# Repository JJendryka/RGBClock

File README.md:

# RGBClock
ESP8266 based RGB clock system for schools with time and schedule synchronization

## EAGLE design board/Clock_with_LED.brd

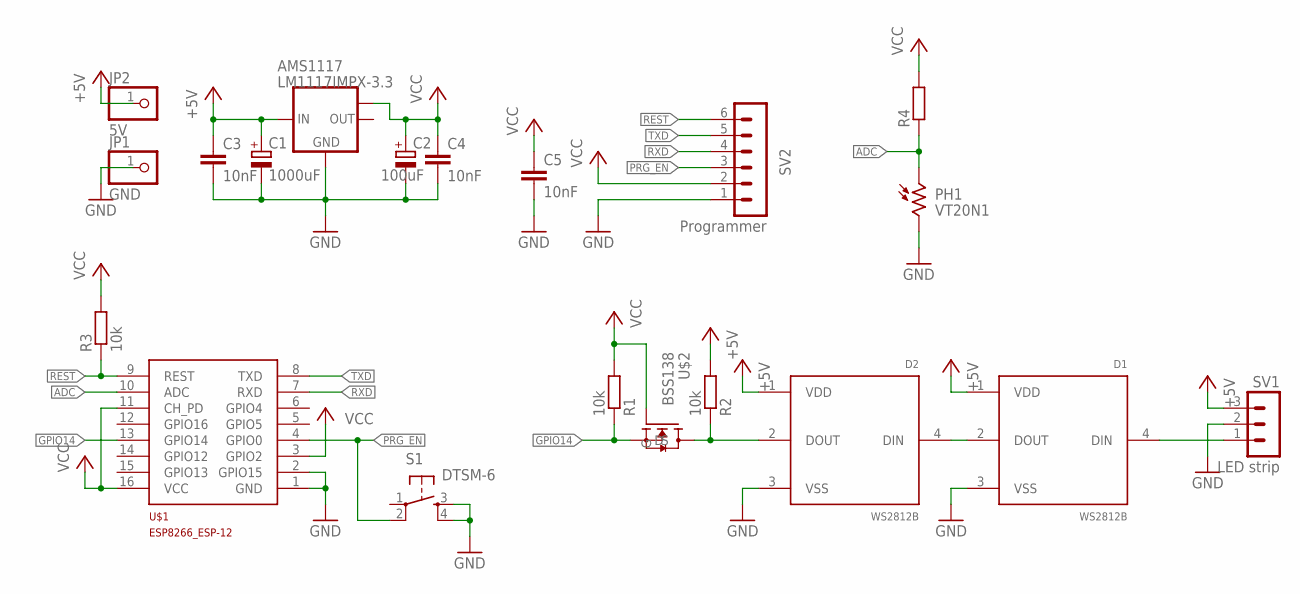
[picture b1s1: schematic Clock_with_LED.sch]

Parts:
AMS1117: LM1117IMPX-3.3; SOT223
C1: 1000uF; TT5D11L
C2: 100uF; TT5D7L
C3, C4, C5: 10nF; C0805
D1, D2: WS2812B; LED_WS2812B
JP1: GND; 1X01
JP2: 5V; 1X01
PH1: VT20N1; TO46-VT200
R1, R2, R3: 10k; R0805
R4: R-EU_R0805; R0805
S1: DTSM-6
SV1: LED strip; MA03-1
SV2: Programmer; MA06-1
U$1: ESP8266_ESP-12; ESP8266-ESP12
U$2: BSS138

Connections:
+5V: AMS1117.3 (IN), C1.+, C3.1, D1.1 (VDD), D2.1 (VDD), JP2.1, R2.2, SV1.3
ADC: PH1.1, R4.1, U$1.10 (ADC)
GND: AMS1117.1 (GND), C1.-, C2.-, C3.2, C4.2, C5.2, D1.3 (VSS), D2.3 (VSS), JP1.1, PH1.2, S1.3, S1.4, SV1.2, SV2.1, U$1.1 (GND), U$1.2 (GPIO15)
GPIO14: R1.1, U$1.13 (GPIO14), U$2.S
unnamed: D1.2 (DOUT), D2.4 (DIN)
unnamed: D1.4 (DIN), SV1.1
unnamed: D2.2 (DOUT), R2.1, U$2.D
PRG_EN: S1.2, SV2.3, U$1.4 (GPIO0)
REST: R3.1, SV2.6, U$1.9 (REST)
RXD: SV2.4, U$1.7 (RXD)
TXD: SV2.5, U$1.8 (TXD)
VCC: AMS1117.TAB (OUT1), C2.+, C4.1, C5.1, R1.2, R3.2, R4.2, SV2.2, U$1.3 (GPIO2), U$1.11 (CH_PD), U$1.16 (VCC), U$2.G

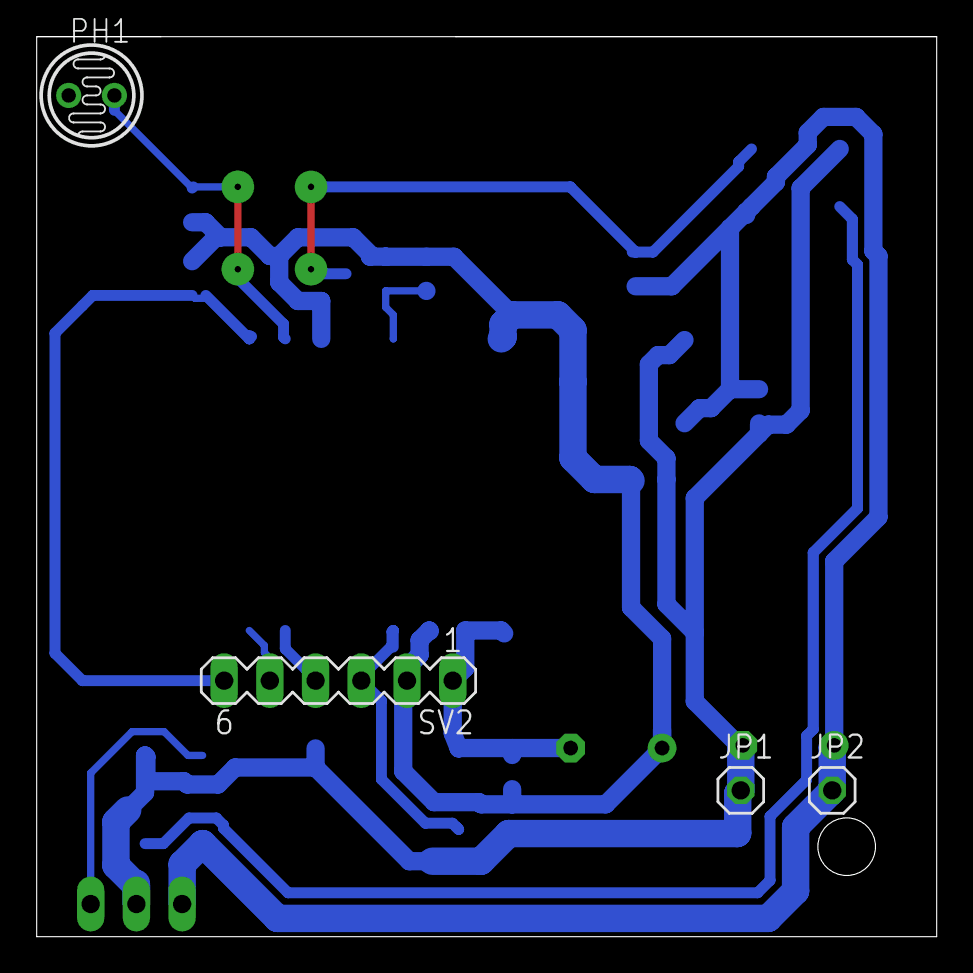
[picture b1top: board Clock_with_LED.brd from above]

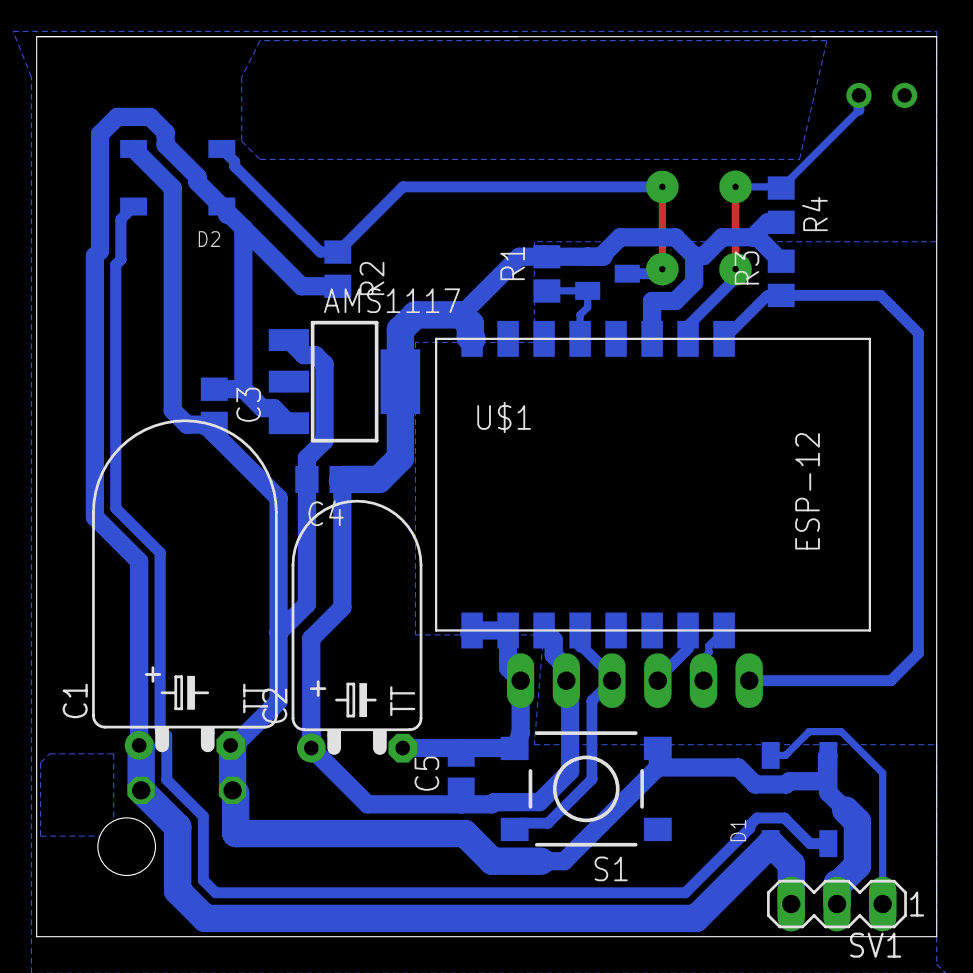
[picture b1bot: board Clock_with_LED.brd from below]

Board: 2 copper layers, 50.0 x 50.0 mm, 20 parts (16 on the bottom side), 12 nets.

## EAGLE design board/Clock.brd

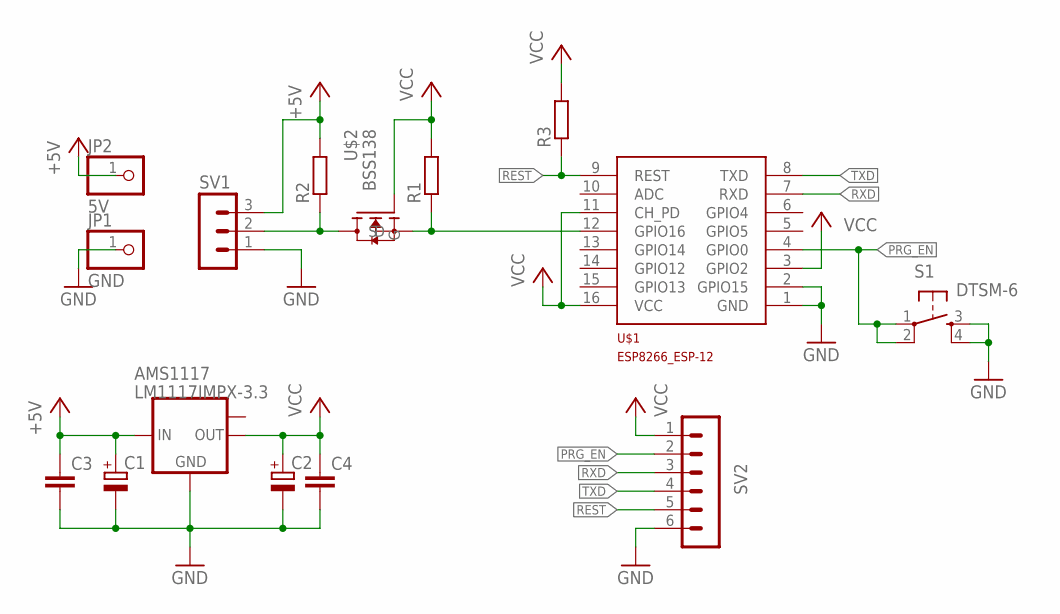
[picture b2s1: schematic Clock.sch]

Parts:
AMS1117: LM1117IMPX-3.3; SOT223
C1, C2: CPOL-EUE3.5-8; E3,5-8
C3, C4: C-EUC0805; C0805
JP1: GND; 1X01
JP2: 5V; 1X01
R1, R2, R3: R-EU_R0805; R0805
S1: DTSM-6
SV1: MA03-1
SV2: MA06-1
U$1: ESP8266_ESP-12; ESP8266-ESP12
U$2: BSS138

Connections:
+5V: AMS1117.3 (IN), C1.+, C3.1, JP2.1, R2.2, SV1.3
GND: AMS1117.1 (GND), C1.-, C2.-, C3.2, C4.2, JP1.1, S1.3, S1.4, SV1.1, SV2.6, U$1.1 (GND), U$1.2 (GPIO15)
unnamed: R2.1, SV1.2, U$2.D
unnamed: R1.1, U$1.12 (GPIO16), U$2.S
PRG_EN: S1.1, S1.2, SV2.2, U$1.4 (GPIO0)
REST: R3.1, SV2.5, U$1.9 (REST)
RXD: SV2.3, U$1.7 (RXD)
TXD: SV2.4, U$1.8 (TXD)
VCC: AMS1117.2 (OUT), C2.+, C4.1, R1.2, R3.2, SV2.1, U$1.3 (GPIO2), U$1.11 (CH_PD), U$1.16 (VCC), U$2.G

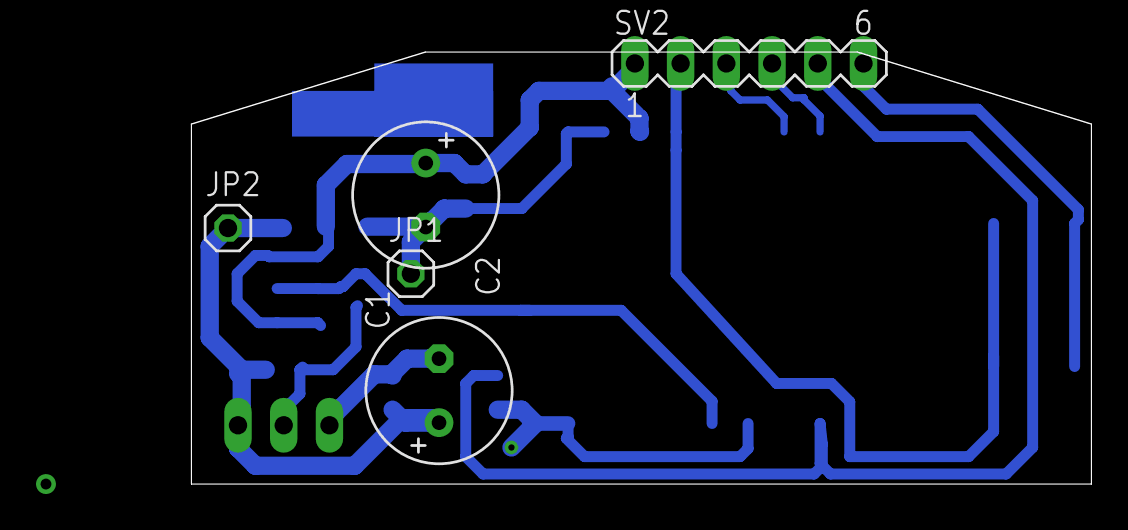
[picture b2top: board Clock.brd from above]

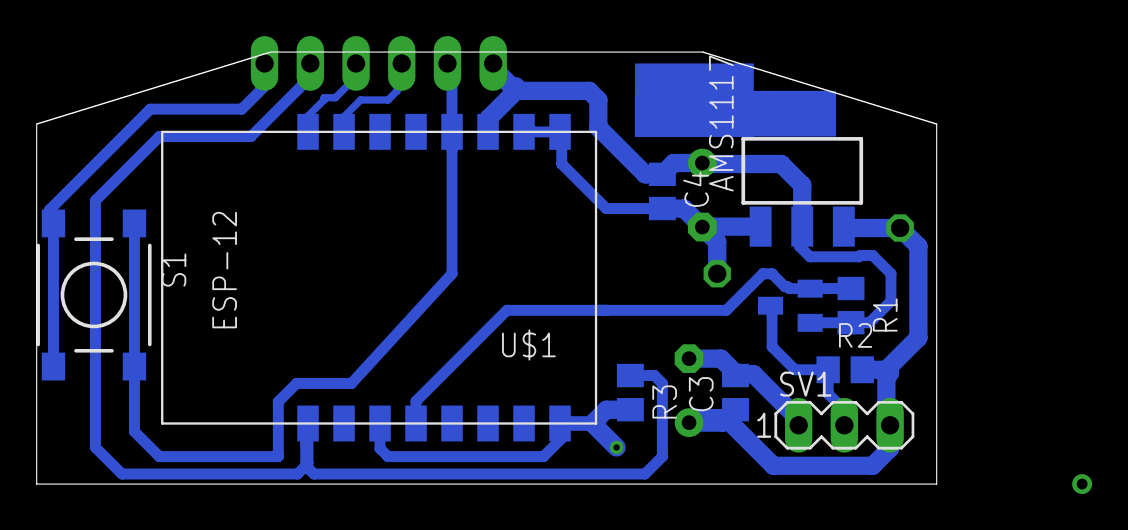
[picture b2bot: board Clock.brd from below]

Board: 2 copper layers, 50.0 x 24.0 mm, 16 parts (10 on the bottom side), 9 nets.

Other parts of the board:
U$3: PIN1

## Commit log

2017-05-25 Added 3d model
2017-05-25 Added Arduino code
2017-05-26 Added board files
2017-05-26 Cleaned up the schematic
2017-05-26 Removed temporary files
2017-05-27 Started work on a new board layout
2017-05-28 Added LEDs and a photoresistor
2017-05-28 Improved clearance
2017-06-01 Added display class
2017-06-02 Removed LEDs, organised PCB files
2017-06-08 Added time downloading and displaying
2017-06-10 Finished most models
2017-06-10 Added a hole for the button
2017-06-10 Prepared the PCB for fabrication
2017-06-25 widened the wire channel, redesigned structural supports in the middle part
